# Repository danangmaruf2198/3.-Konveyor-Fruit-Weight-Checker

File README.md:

# 3.-Konveyor-Fruit-Weight-Checker
this project is about konveyor that used to check the weight of some fruit. also there is some interface button and lcd to control the process and parameter inside the konveyor.

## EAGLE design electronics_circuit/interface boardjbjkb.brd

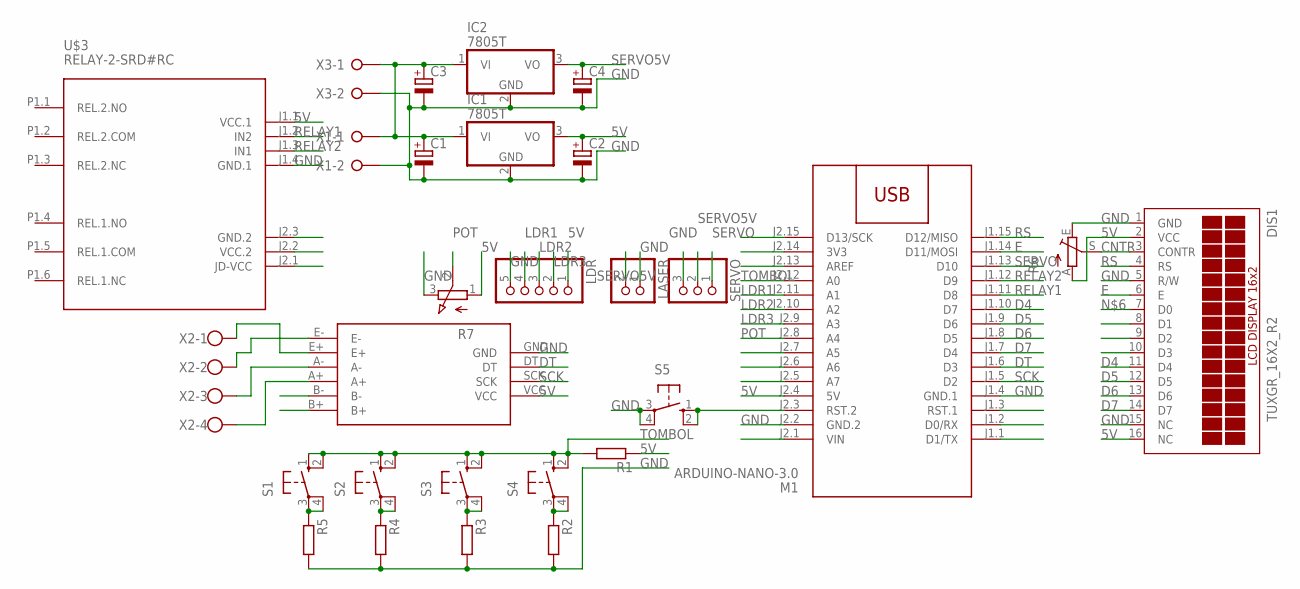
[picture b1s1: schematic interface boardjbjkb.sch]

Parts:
C1, C2, C3, C4: CPOL-EUE2.5-7; E2,5-7
DIS1: TUXGR_16X2_R2
IC1, IC2: 7805T; TO220H
LASER: PINHD-1X2; 1X02
LDR: PINHD-1X5; 1X05
M1: ARDUINO-NANO-3.0
R1, R2, R3, R4, R5: R-EU_0207/10; 0207/10
R6: TRIM_EU-B25P; B25P
R7: 3RP/1610N
S1, S2, S3, S4: 40-XX; B3F-40XX
S5: 10-XX; B3F-10XX
SERVO: PINHD-1X3; 1X03
U$2: HX711
U$3: RELAY-2-SRD#RC
X1, X3: W237-02P; W237-132
X2: W237-4

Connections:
5V: C2.+, DIS1.2 (VCC), DIS1.16 (NC), IC1.3 (VO), LDR.1, M1.J2.4 (5V), R1.1, R6.A, R7.1 (A), U$2.VCC, U$3.J1.1 (VCC.1)
CNTR: DIS1.3 (CONTR), R6.S
D4: DIS1.11 (D4), M1.J1.10 (D7)
D5: DIS1.12 (D5), M1.J1.9 (D6)
D6: DIS1.13 (D6), M1.J1.8 (D5)
D7: DIS1.14 (D7), M1.J1.7 (D4)
DT: M1.J1.6 (D3), U$2.DT
E: DIS1.6 (E), M1.J1.14 (D11/MOSI)
GND: C1.-, C2.-, C3.-, C4.-, DIS1.1 (GND), DIS1.5 (R/W), DIS1.15 (NC), IC1.2 (GND), IC2.2 (GND), LASER.1, LDR.5, M1.J1.4 (GND.1), M1.J2.2 (GND.2), R2.2, R3.2, R4.2, R5.2, R6.E, R7.3 (E), S5.3, S5.4 (P1), SERVO.3, U$2.GND, U$3.J1.4 (GND.1), X1.2, X3.2
LDR1: LDR.4, M1.J2.11 (A1)
LDR2: LDR.3, M1.J2.10 (A2)
LDR3: LDR.2, M1.J2.9 (A3)
unnamed: C1.+, C3.+, IC1.1 (VI), IC2.1 (VI), X1.1, X3.1
unnamed: U$2.E-, X2.2
unnamed: U$2.E+, X2.1
unnamed: R2.1, S4.3, S4.4 (P1)
unnamed: R3.1, S3.3, S3.4 (P1)
unnamed: R4.1, S2.3, S2.4 (P1)
unnamed: R5.1, S1.3, S1.4 (P1)
unnamed: U$2.A-, X2.3
unnamed: U$2.A+, X2.4
unnamed: M1.J2.3 (RST.2), S5.1 (S), S5.2 (S1)
POT: M1.J2.8 (A4), R7.2 (S)
RELAY1: M1.J1.11 (D8), U$3.J1.2 (IN2)
RELAY2: M1.J1.12 (D9), U$3.J1.3 (IN1)
RS: DIS1.4 (RS), M1.J1.15 (D12/MISO)
SCK: M1.J1.5 (D2), U$2.SCK
SERVO: M1.J1.13 (D10), SERVO.1
SERVO5V: C4.+, IC2.3 (VO), LASER.2, SERVO.2
TOMBOL: M1.J2.12 (A0), R1.2, S1.1 (S), S1.2 (S1), S2.1 (S), S2.2 (S1), S3.1 (S), S3.2 (S1), S4.1 (S), S4.2 (S1)

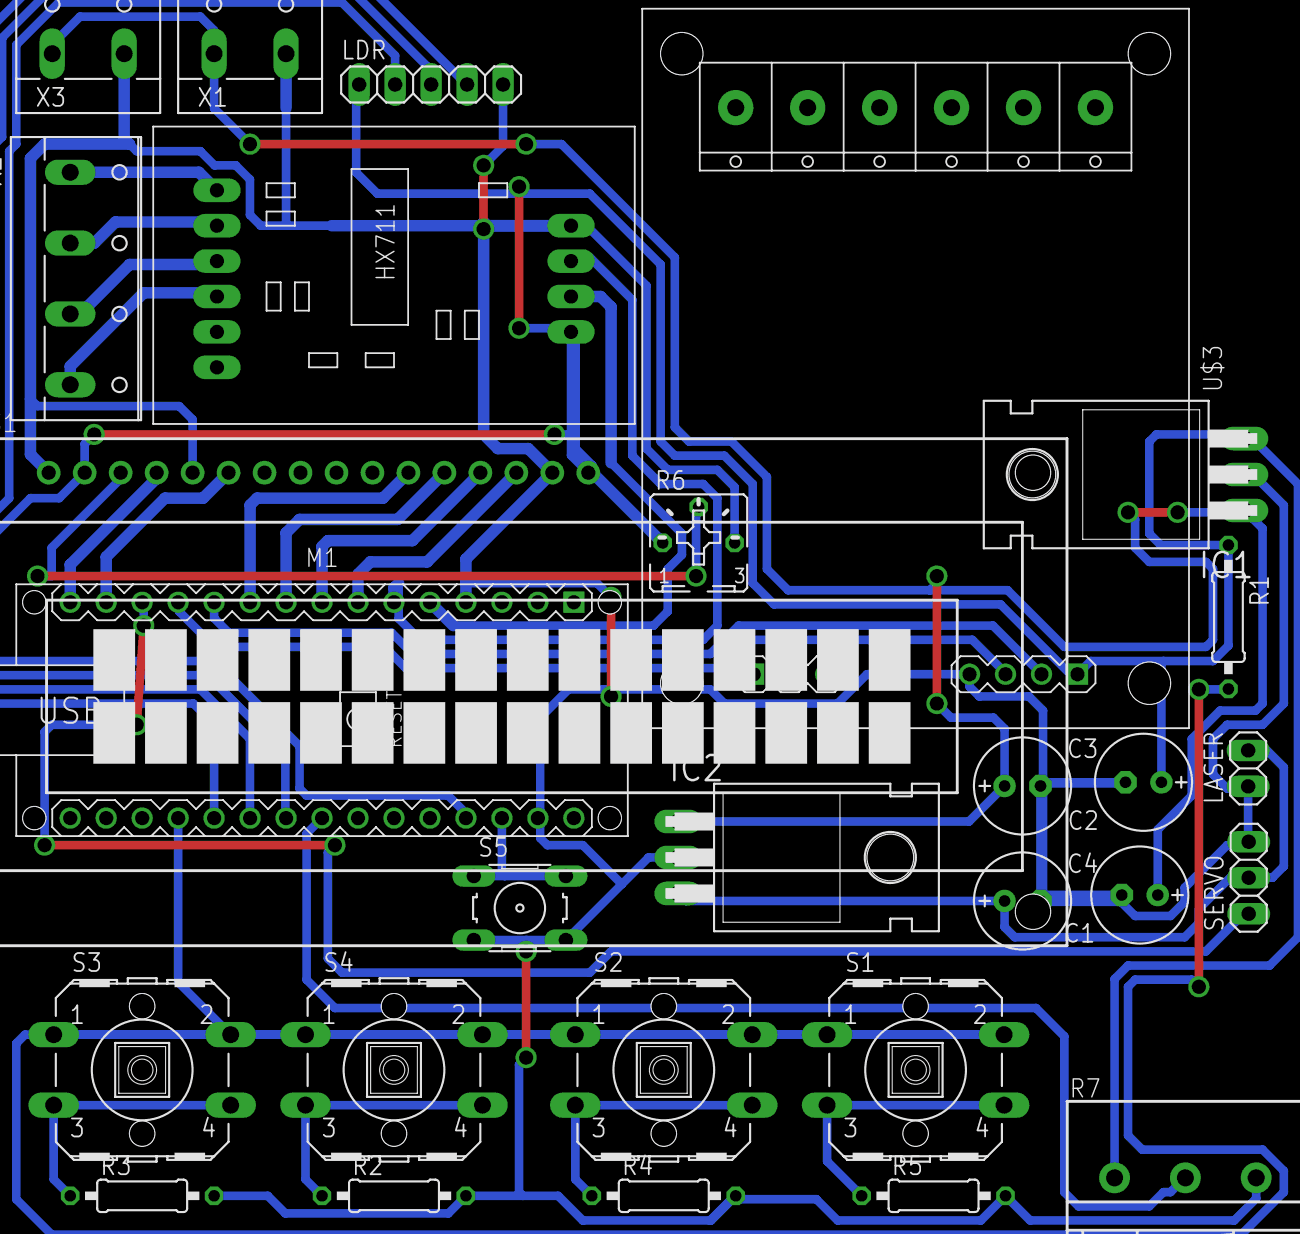
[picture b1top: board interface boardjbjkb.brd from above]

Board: 2 copper layers, 28 parts (0 on the bottom side), 30 nets.

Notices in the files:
parts and their libraries:
diy-modules: Released under the Creative Commons Attribution 4.0 International License: http://creativecommons.org/licenses/by/4.0
